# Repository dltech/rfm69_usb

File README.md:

# rfm69_usb
RFM69 based usb stick. Virtual wireless com port.

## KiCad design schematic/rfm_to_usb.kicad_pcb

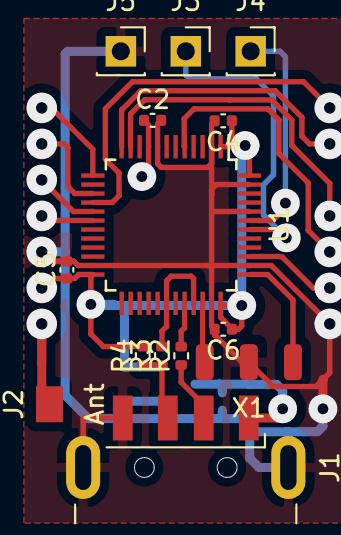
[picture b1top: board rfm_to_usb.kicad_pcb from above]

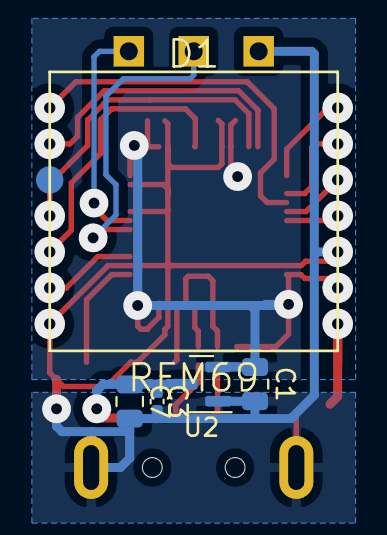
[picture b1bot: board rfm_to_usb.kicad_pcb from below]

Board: 2 copper layers, 19 parts (5 on the bottom side), 21 nets.

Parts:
C1, C7: 10uF; C_0805_2012Metric
C2, C3, C4, C5, C6: 0.1uF; C_0402_1005Metric
D1: RFM69
J1: USB_A; USB_A_CNCTech_1001-011-01101_Horizontal
J2: Ant; pin_smd
J3: UART_TX; PinSocket_1x01_P2.54mm_Vertical
J4: UART_RX; PinSocket_1x01_P2.54mm_Vertical
J5: GND; PinSocket_1x01_P2.54mm_Vertical
R2, R3: 22R; R_0402_1005Metric
R4: 1.5k; R_0402_1005Metric
U1: STM32F103C8; TQFP-48_7x7mm_P0.5mm
U2: XC6206-33; SOT-23
X1: SWD_CON; 3WIRE_PADS

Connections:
+3V3: C1.1, C2.1, C4.1, C5.1, C6.1, D1.2, R4.2, U1.1, U1.9, U1.24, U1.36, U1.48, U2.2
+5V: C3.1, C7.1, J1.1, U2.3
/DIO0: D1.9, U1.12
/DIO1: D1.11, U1.11
/MISO: D1.8, U1.16
/MOSI: D1.5, U1.17
/NSS: D1.7, U1.13
/SCK: D1.6, U1.15
GND: C1.2, C2.2, C3.2, C4.2, C5.2, C6.2, C7.2, D1.3, D1.14, J1.4, J1.5, J5.1, U1.2, U1.8, U1.23, U1.35, U1.38, U1.44, U1.47, U2.1, X1.2
unnamed: D1.1, J2.1
unnamed: D1.4, U1.18
unnamed: D1.12, U1.5
unnamed: D1.13, U1.39
unnamed: J1.2, R2.1
unnamed: J1.3, R3.1, R4.1
unnamed: J3.1, U1.42
unnamed: J4.1, U1.43
unnamed: R2.2, U1.32
unnamed: R3.2, U1.30, U1.33
unnamed: U1.34, X1.3
unnamed: U1.37, X1.1

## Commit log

2021-06-09 new schematic, old code
2021-06-09 photo
2021-06-09 ридми
2021-06-10 err in pcb
2022-03-06 add uart, 2.8 mm lenght
2022-05-03 makefile build
2022-05-03 prety make
2022-05-04 cubeide build
